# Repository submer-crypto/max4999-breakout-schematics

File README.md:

# MAX4999 breakout board

EAGLE schematics for the [MAX4999](https://www.maximintegrated.com/en/products/analog/analog-switches-multiplexers/MAX4999.html) breakout board. The MAX4999 is an USB 2.0 Hi-Speed multiplexer using a TQFN-32 (QFN-32) package.

The breakout board exposes all the 32 pins of the MAX4999. The breakout pins are 2.54mm (0.1") apart from each other with 16 pins on each side. It fits on a standard breadboard for prototyping.

Top and bottom of printed board.

Assembled board with the MAX4999.

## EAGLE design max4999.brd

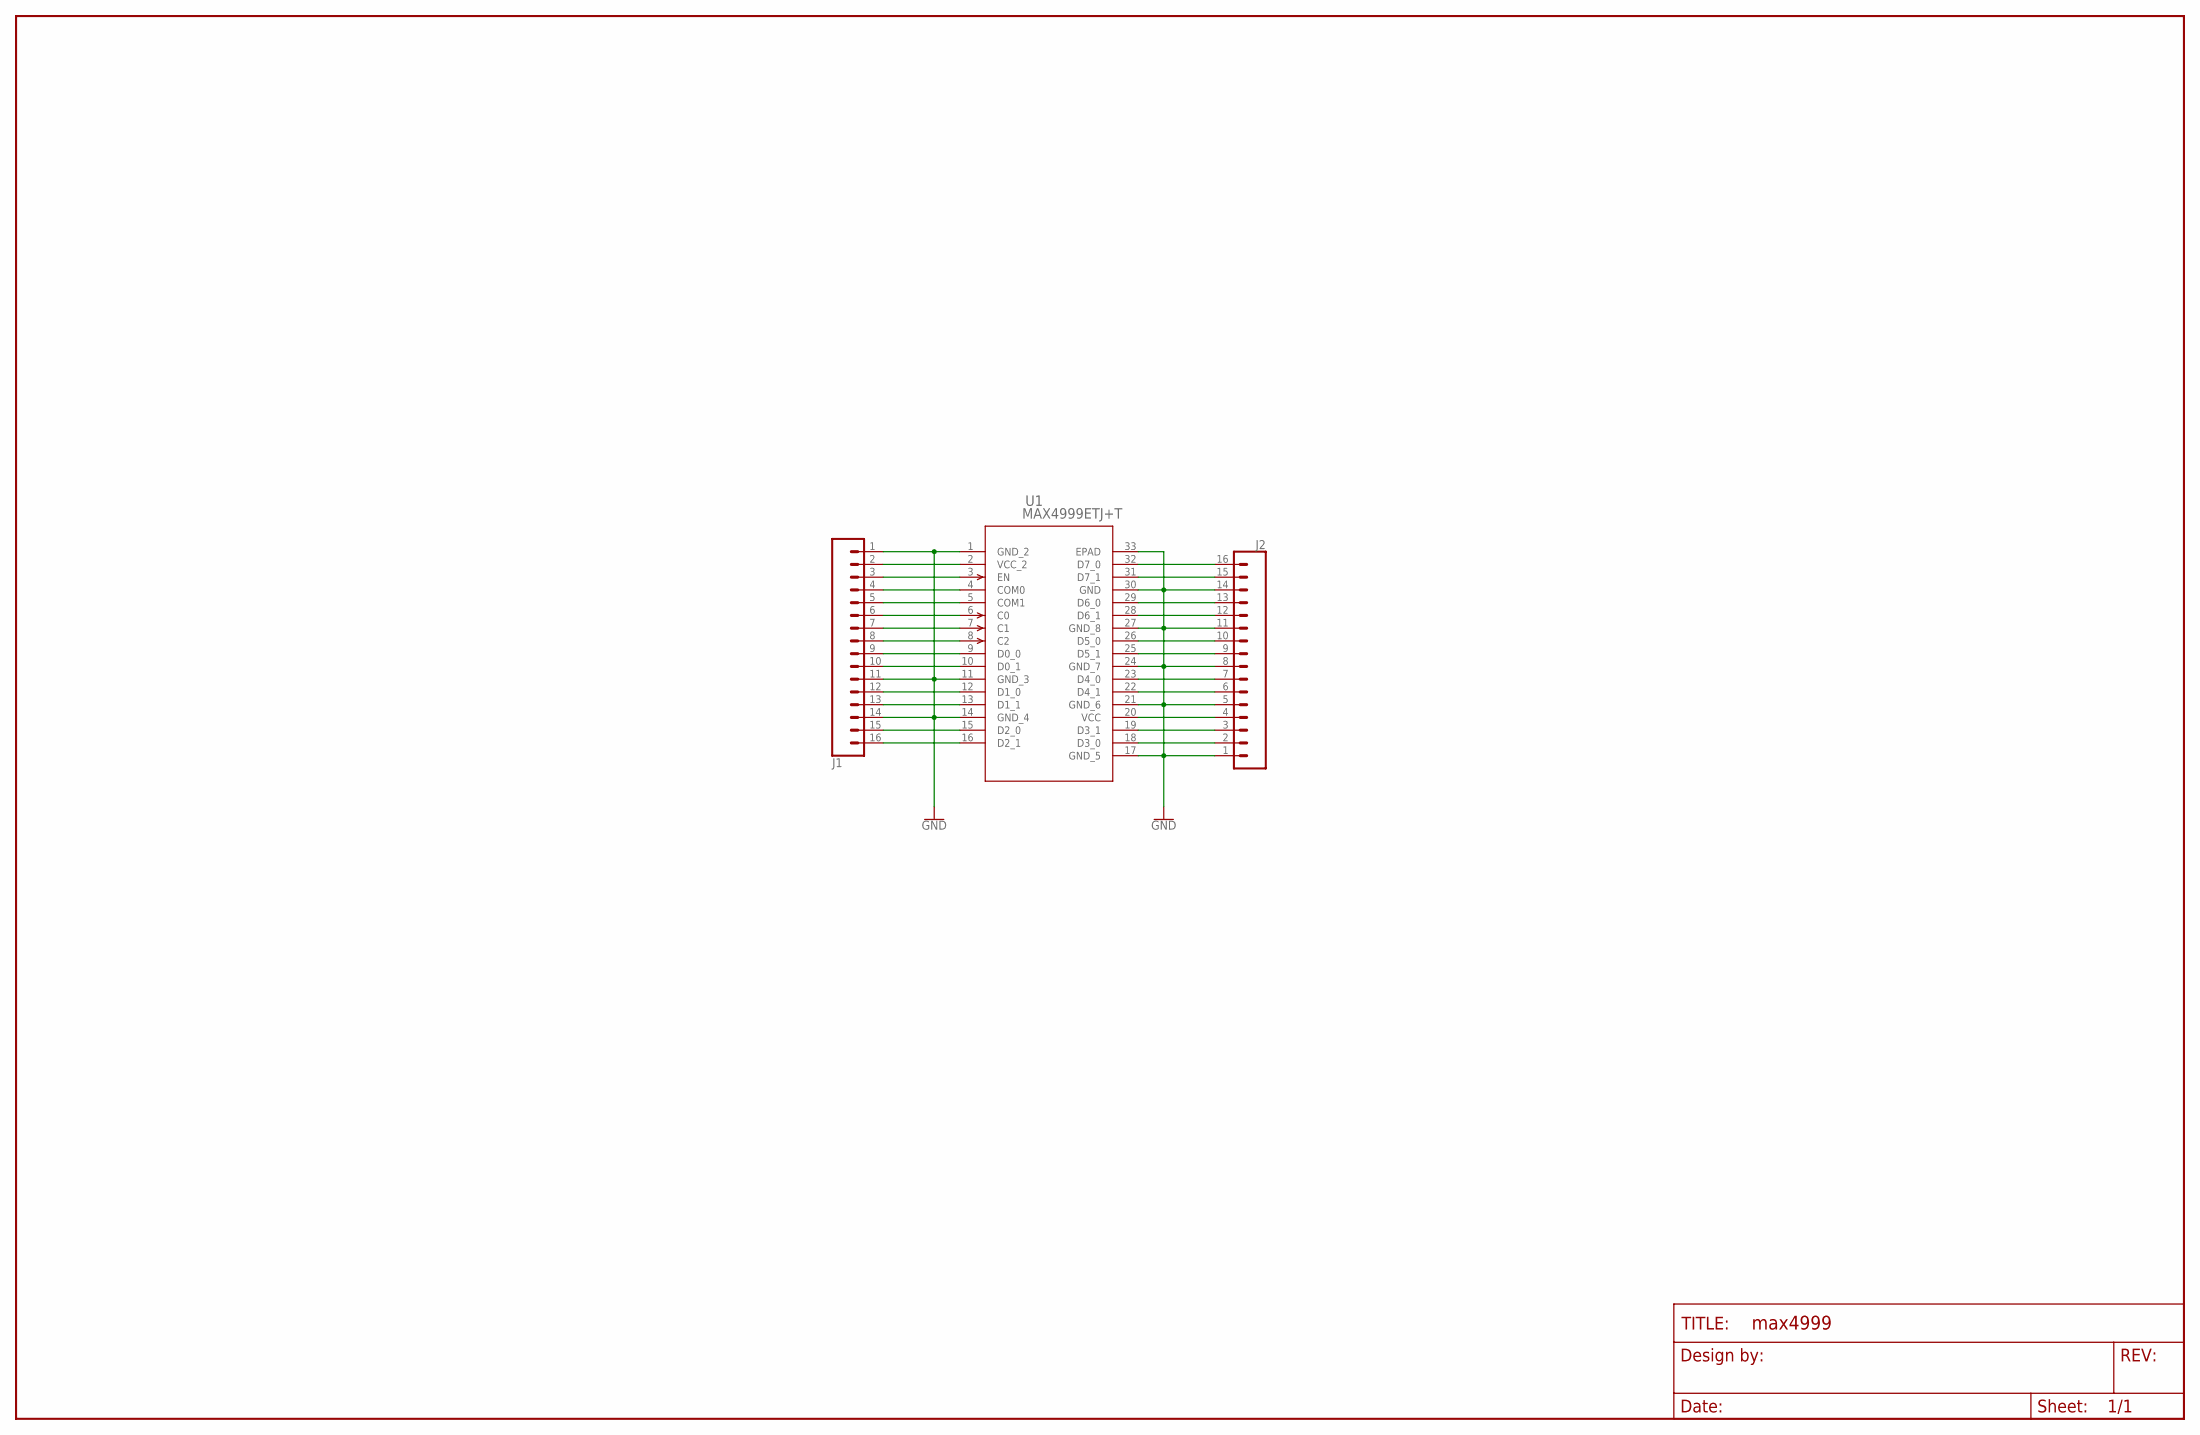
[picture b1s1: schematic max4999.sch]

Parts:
FRAME1: FRAME-LEDGERNO_FOOTPRINT; DUMMY
J1, J2: CONN_161X16_NO_SILK; 1X16_NO_SILK
U1: MAX4999ETJ+T; 21-0140_T3255+4_MXM

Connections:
GND: J1.1, J1.11, J1.14, J2.1, J2.5, J2.8, J2.11, J2.14, U1.1 (GND_2), U1.11 (GND_3), U1.14 (GND_4), U1.17 (GND_5), U1.21 (GND_6), U1.24 (GND_7), U1.27 (GND_8), U1.30 (GND), U1.33 (EPAD)
unnamed: J1.2, U1.2 (VCC_2)
unnamed: J1.3, U1.3 (EN)
unnamed: J1.4, U1.4 (COM0)
unnamed: J1.5, U1.5 (COM1)
unnamed: J1.6, U1.6 (C0)
unnamed: J1.7, U1.7 (C1)
unnamed: J1.8, U1.8 (C2)
unnamed: J1.9, U1.9 (D0_0)
unnamed: J1.10, U1.10 (D0_1)
unnamed: J1.12, U1.12 (D1_0)
unnamed: J1.13, U1.13 (D1_1)
unnamed: J1.15, U1.15 (D2_0)
unnamed: J1.16, U1.16 (D2_1)
unnamed: J2.16, U1.32 (D7_0)
unnamed: J2.15, U1.31 (D7_1)
unnamed: J2.13, U1.29 (D6_0)
unnamed: J2.12, U1.28 (D6_1)
unnamed: J2.10, U1.26 (D5_0)
unnamed: J2.9, U1.25 (D5_1)
unnamed: J2.7, U1.23 (D4_0)
unnamed: J2.6, U1.22 (D4_1)
unnamed: J2.4, U1.20 (VCC)
unnamed: J2.3, U1.19 (D3_1)
unnamed: J2.2, U1.18 (D3_0)

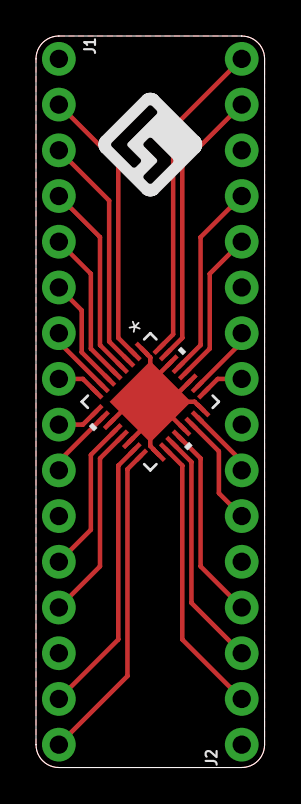
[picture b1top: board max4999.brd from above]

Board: 2 copper layers, 12.7 x 40.6 mm, 4 parts (0 on the bottom side), 25 nets.

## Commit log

2022-06-13 Add logo to silk
2022-06-22 Fix silk label placing
2022-07-01 Add readme and images
2022-07-04 Clarify pins in readme
2022-07-04 Fix readme title

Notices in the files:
parts and their libraries:
SparkFun-Aesthetics: Licensing: Creative Commons ShareAlike 4.0 International - https://creativecommons.org/licenses/by-sa/4.0
COPYRIGHT: Copyright (C) 2022 Ultra Librarian. All rights reserved.
SparkFun-Aesthetics: Released under the Creative Commons Attribution Share-Alike 4.0 License
